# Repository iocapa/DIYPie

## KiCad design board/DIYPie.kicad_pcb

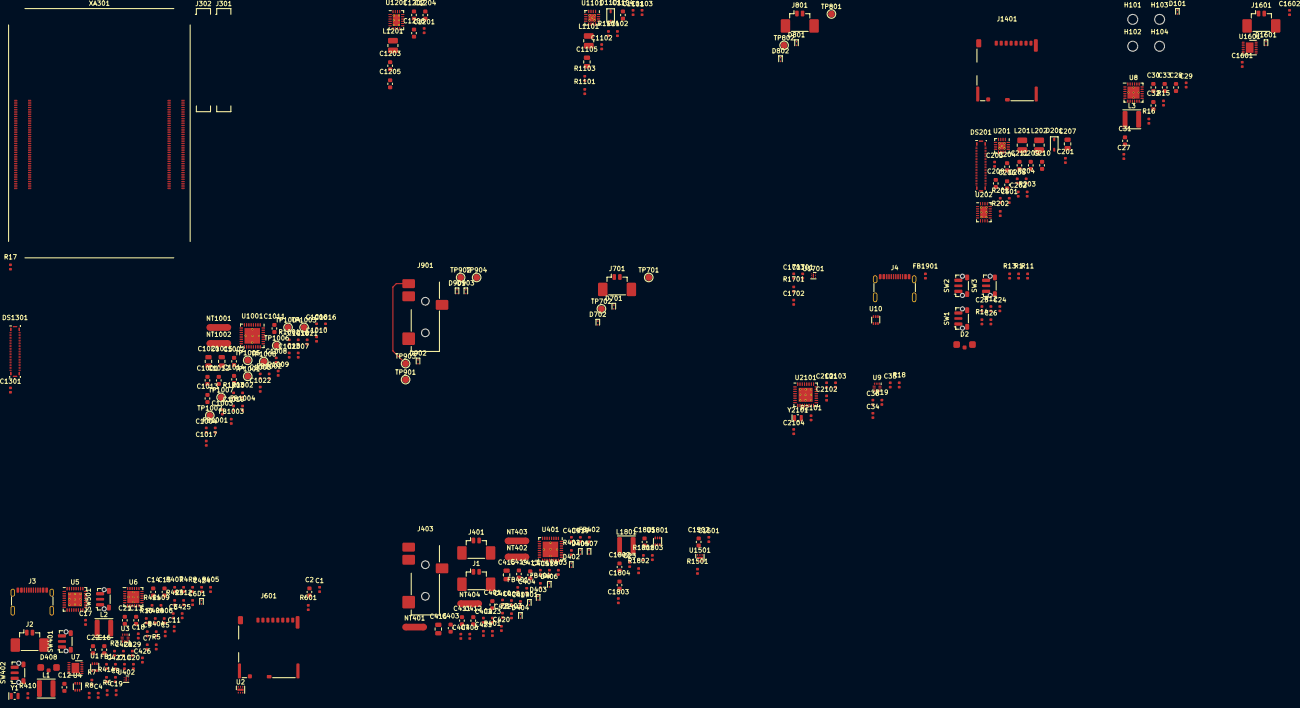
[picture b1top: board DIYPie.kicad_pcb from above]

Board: 6 copper layers, 289 parts (0 on the bottom side), 166 nets.

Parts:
C1, C20, C203, C405, C408, C417, C424, C425, C426, C1005, C1008, C1019, C1103, C1501, C1602, C1701, C1702, C1703: 470n; C_0402_1005Metric
C2, C13, C14, C15, C16, C21, C22, C28, C31, C32, C33, C209, C210, C211, C411, C412, C413, C414, C1011, C1012, C1013, C1014, C1204, C1205, C1206, C1502, C1804, C1805: 10u; C_0603_1608Metric
C3, C11, C17, C19, C34, C36, C1803: 220p; C_0402_1005Metric
C4, C5, C6, C10, C27, C35, C201, C202, C205, C501, C1101, C1102, C1201, C1301, C2101, C2104: 1u; C_0402_1005Metric
C7, C8, C2102, C2103: 12p; C_0402_1005Metric
C9, C29, C418, C419, C1018, C1023: 47n; C_0402_1005Metric
C12, C30, C204, C206, C208, C401, C403, C1001, C1002, C1104, C1202, C1203, C1802: 4u7; C_0603_1608Metric
C18, C23, C24, C25, C26, C402, C404, C406, C407, C409, C410, C427, C428, C429, C1003, C1004, C1006, C1007, C1009, C1010, C1601: 0u1; C_0402_1005Metric
C207, C1105: 4u7; C_0805_2012Metric
C415, C416, C1015, C1020: 47u; C_0805_2012Metric
C420, C421, C422, C423, C1016, C1017, C1021, C1022: 470p; C_0402_1005Metric
D1, D401, D402, D403, D404, D405, D406, D407, D701, D702, D801, D802, D901, D902, D903, D1601: DF2B7AFS; D_SOD-923
D2, D408: STATUS; KINGBRIGHT_APBA3010
D101: XBP1010-G; D_SOD-923
D201, D1101: PMEG4010CEJ; D_SOD-323F
DS201, DS1301: LPM035M407B; KYOCERA_245863050104829+
FB1, FB401, FB402, FB403, FB404, FB1001, FB1002, FB1003, FB1004, FB1901: 120R; L_0402_1005Metric
H101, H102, H103, H104: Hole; MountingHole_2.2mm_M2
J1: SPK_L; MOLEX_533980267
J2, J1601: BAT; MOLEX_533980267
J3, J4: MOLEX_2171790001
J301, J302: DF40C-100DS-0.4V(51); HIROSE_DF40C-100DS-0.4V(51)_NoPads
J401, J701, J801: SPK_R; MOLEX_533980267
J403, J901: HP; CUI_DEVICES_SJ-43514-SMT
J601, J1401: MOLEX_5033981892
L1, L2, L3, L1801: 1u; L_TYA4020
L201, L202, L1101, L1201: 4u7; L_1008_2520Metric
NT401, NT402, NT403, NT404, NT1001, NT1002: Net-Tie_2; NetTie-2_SMD_Pad1.5mm
R1, R11, R402, R403, R410, R411, R1001, R1003: 100R; R_0402_1005Metric
R3, R5, R6, R10, R15, R16, R18, R406, R407, R409: 10K; R_0402_1005Metric
R4, R7, R8, R19, R203, R405, R601, R1103, R1501, R1701, R1801, R1802: 732K; R_0402_1005Metric
R9, R12, R13, R14, R17, R408, R412, R413, R414, R1803: 100K; R_0402_1005Metric
R201, R204, R404, R1101, R1104, R2101: 34K; R_0402_1005Metric
R202, R1102: 82K; R_0402_1005Metric
R401, R1002: 2K2; R_0402_1005Metric
SW1, SW401: POWER; CKCOMPONENTS_PTS845VM20PSMTR4LFS
SW2, SW501: VOL+; CKCOMPONENTS_PTS845VM20PSMTR4LFS
SW3, SW402: VOL-; CKCOMPONENTS_PTS845VM20PSMTR4LFS
TP701, TP702, TP801, TP802, TP901, TP902, TP903, TP904, TP1001, TP1002, TP1003, TP1004, TP1005, TP1006, TP1007, TP1008: TestPoint; TestPoint_Pad_D1.5mm
U1, U1801: TPS61023; SOT-563
U2, U1501: MIC94305; TDFN1616-6LD-PL-1
U3, U9: FUSB303BTMX; ON_X2QFN-12_1.6x1.6mm_P0.4mm
U4, U10: DT1446-04V-7; SOT-563
U5, U2101: ATmega808-M; MICROCHIP_VQFN-32_RXB
U6, U8: BQ24259RGE; TI_BQ24259RGE
U7, U1601: MAX17260SETD+; MAXIM_TDFN-14-EP-T1433-2C
U201, U1101: TPS61176; TI_TPS61176RTE
U202, U1201: TPS65132W; TI_TPS65132WRVC
U401, U1001: TLV320AIC3110IRHB; TI_TLV320AIC3110
U402, U1701: AP7342; DIODES_X2-DFN1212-6
XA301: CM4; CM4_LOW_PROFILE_NoHoles
Y1, Y2101: 32K768; WE_830050789

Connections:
+1V8: C401.1, C402.1, C501.2, C1301.2, DS201.2 (VDDI), DS201.4 (VDDI), DS1301.2 (VDDI), DS1301.4 (VDDI), U401.3 (DVDD), XA301.88 (CM4_1.8V), XA301.90 (CM4_1.8V)
+3V3: C1.1, C4.2, C5.2, C10.2, C35.2, C202.2, C205.2, C403.1, C404.1, C425.1, C426.1, C1102.2, C1201.2, C2101.2, C2104.2, D2.1 (A), D408.1 (A), NT403.1, R3.1, R7.1, R10.1, R12.1, R13.1, R14.1, R18.1, R404.1, R406.1, R407.1, R409.1, R412.1, R413.1, R414.1, R601.1, R2101.1, U2.5 (VIN), U2.6 (VIN), U3.12 (VDD), U5.18 (AVDD), U5.28 (VDD), U9.12 (VDD), U201.15 (VIN), U202.4 (VIN), U401.2 (IOVDD), U402.1 (VO1), U402.2 (VO2), U1101.15 (VIN), U1201.4 (VIN), U2101.18 (AVDD), U2101.28 (VDD), XA301.78 (GPIO_VREF), XA301.84 (CM4_3.3V), XA301.86 (CM4_3.3V)
+5V: C6.2, C14.1, C15.1, C16.1, C19.2, C21.1, C22.1, C27.2, C32.1, C204.1, C206.1, C424.1, C1104.1, C1202.1, J3.A4 (VBUS), J3.A9 (VBUS), J3.B4 (VBUS), J3.B9 (VBUS), J4.A4 (VBUS), J4.A9 (VBUS), J4.B4 (VBUS), J4.B9 (VBUS), L1.2, L2.1, L201.1, L202.1, L1101.1, L1201.1, NT404.1, R8.1, U1.3 (VIN), U1.6 (VOUT), U3.4 (VBUS_DET), U4.5 (VBUS), U6.1 (VBUS), U6.13 (BAT), U6.14 (BAT), U6.15 (SYS), U6.16 (SYS), U6.24 (VBUS), U8.1 (VBUS), U8.13 (BAT), U8.14 (BAT), U8.24 (VBUS), U9.4 (VBUS_DET), U10.5 (VBUS), U402.5 (VIN), U402.6 (EN1), XA301.77 (+5V), XA301.79 (+5V), XA301.81 (+5V), XA301.83 (+5V), XA301.85 (+5V), XA301.87 (+5V)
/3V3 Regulators/EN2: R1701.1, U1701.4 (EN2)
/3V3 Regulators/VIN: C1701.1, U1701.5 (VIN), U1701.6 (EN1)
/3V3 Regulators/VOUT1: C1702.1, U1701.1 (VO1)
/3V3 Regulators/VOUT2: C1703.1, U1701.2 (VO2)
/5V Regulator/EN: C23.1, R1801.1, U1801.2 (EN)
/5V Regulator/VIN: C1802.1, L1801.1, U1801.3 (VIN)
/5V Regulator/VOUT: C1803.1, C1804.1, C1805.1, R1802.1, U1801.6 (VOUT)
/Audio CODEC/AVDD: C1006.1, C1009.1, C1011.1, C1013.1, U1001.17 (AVDD), U1001.28 (HPVDD)
/Audio CODEC/DVDD: C1002.1, C1004.1, U1001.3 (DVDD)
/Audio CODEC/HP_L: C1020.2, R1003.1
/Audio CODEC/HP_R: C1015.2, R1001.1
/Audio CODEC/IOVDD: C1001.1, C1003.1, U1001.2 (IOVDD)
/Audio CODEC/SPL_M: C1017.2, FB1002.1
/Audio CODEC/SPL_P: C1016.2, FB1001.1
/Audio CODEC/SPR_M: C1022.2, FB1004.1
/Audio CODEC/SPR_P: C1021.2, FB1003.1
/Audio CODEC/SPVDD: C1007.1, C1010.1, C1012.1, C1014.1, U1001.21 (SPLVDD), U1001.24 (SPRVDD)
/Audio CODEC/hpl: C1020.1, U1001.27 (HPL)
/Audio CODEC/hpr: C1015.1, U1001.30 (HPR)
/Audio CODEC/i2s_din: TP1007.1, U1001.4 (DOUT)
/Audio CODEC/i2s_dout: TP1006.1, U1001.5 (DIN)
/Audio CODEC/i2s_fs: TP1005.1, U1001.6 (WCLK)
/Audio CODEC/i2s_sclk: TP1004.1, U1001.7 (BCLK)
/Audio CODEC/int: TP1002.1, U1001.32 (GPIO1)
/Audio CODEC/mclk: TP1003.1, U1001.8 (MCLK)
/Audio CODEC/mic: C1019.2, U1001.14 (MIC1RP)
/Audio CODEC/micbias: R1002.2, U1001.12 (MICBIAS)
/Audio CODEC/micdet: C1019.1, R1002.1, U1001.11 (VOL/MICDET)
/Audio CODEC/reset: TP1001.1, U1001.31 (~RESET~)
/Audio CODEC/splm: FB1002.2, U1001.19 (SPLM)
/Audio CODEC/splp: FB1001.2, U1001.22 (SPLP)
/Audio CODEC/sprm: FB1004.2, U1001.23 (SPRM)
/Audio CODEC/sprp: FB1003.2, U1001.26 (SPRP)
/Audio/aud_hpl: C416.1, U401.27 (HPL)
/Audio/aud_hpr: C415.1, U401.30 (HPR)
/Audio/aud_mic: C417.1, U401.14 (MIC1RP)
/Audio/aud_micbias: R401.2, U401.12 (MICBIAS)
/Audio/aud_micdet: C417.2, D405.2 (A), J403.S, R401.1, U401.11 (VOL/MICDET)
/Audio/aud_splm: FB403.2, U401.19 (SPLM)
/Audio/aud_splp: FB404.2, U401.22 (SPLP)
/Audio/aud_sprm: FB401.2, U401.23 (SPRM)
/Audio/aud_sprp: FB402.2, U401.26 (SPRP)
/Backlight/disp_led+: C1105.1, D1101.1 (K), R1103.1
/Battery/scb_vbat_sns: C1601.1, U1601.6 (BATT)
/Bias/disp_avdd: C1204.1, U1201.15 (OUTP), U1201.16 (OUTP)
/Bias/disp_avee: C1206.1, U1201.9 (OUTN)
/Buttons & LEDs/scb_sw_pow: C24.1, R12.2, SW1.2
/Buttons & LEDs/scb_sw_vol+: C25.1, R13.2, SW2.2
/Buttons & LEDs/scb_sw_vol-: C26.1, R14.2, SW3.2
/Compute module 4/scb_global_en: R17.1, XA301.99 (GLOBAL_EN)
/Display1/disp_avdd: C210.1, DS201.3 (AVDD), U202.15 (OUTP), U202.16 (OUTP)
/Display1/disp_avee: C211.1, DS201.7 (AVEE), U202.9 (OUTN)
/Display1/disp_led1-: DS201.45 (LED1-), U201.11 (IFB1)
/Display1/disp_led2-: DS201.47 (LED2-), U201.7 (IFB4)
/Display1/disp_led+: C207.1, D201.1 (K), DS201.41 (LED+), R203.1
/Display1/disp_pwm: DS201.48 (LEDPWM), U201.1 (PWM/EN)
/Headpnones/HP_L: D901.2 (A), J901.T, TP901.1
/Headpnones/HP_R: D902.2 (A), J901.R1, TP902.1
/Headpnones/MIC: D903.2 (A), J901.S, TP903.1
/Left speaker/SP_M: D801.2 (A), J801.1, TP801.1
/Left speaker/SP_P: D802.2 (A), J801.2, TP802.1
/Memory/mem_pwr: R601.2, U2.4 (EN)
/Right speaker/SP_M: D701.2 (A), J701.1, TP701.1
/Right speaker/SP_P: D702.2 (A), J701.2, TP702.1
/SD Power/EN: R1501.2, U1501.4 (EN)
/SD Power/VIN: C1501.1, R1501.1, U1501.5 (VIN), U1501.6 (VIN)
/SD Power/VOUT: C1502.1, U1501.1 (VOUT), U1501.2 (VOUT)
/System Control Block/scb_3v3a_en: R405.1, U402.4 (EN2)
/System Control Block/scb_5v_en: C17.2, R7.2, U1.2 (EN)
/System Control Block/scb_dbg_rst: R404.2, U5.26 (PF6/~RESET~)
/System Control Block/scb_global_en: R408.1, U5.14 (PD4)
/System Control Block/scb_int_bc: R406.2, U5.12 (PD2), U6.7 (INT)
/System Control Block/scb_int_fg: R10.2, U5.10 (PD0), U7.12 (ALRT)
/System Control Block/scb_int_usbc: R3.2, U3.6 (INT_N/OUT3), U5.11 (PD1)
/System Control Block/scb_led_g: R411.2, U5.23 (PF3)
/System Control Block/scb_loc_scl: R407.2, U3.8 (SCL/OUT2), U5.1 (PA3), U6.5 (SCL), U7.14 (SCL)
/System Control Block/scb_loc_sda: R409.2, U3.7 (SDA/OUT1), U5.32 (PA2), U6.6 (SDA), U7.13 (SDA)
/System Control Block/scb_sw_pow: C427.1, R412.2, SW401.2
/System Control Block/scb_sw_vol+: C428.1, R413.2, SW501.2
/System Control Block/scb_sw_vol-: C429.1, R414.2, SW402.2
/System Control Block/scb_usb_cc1: C3.2, J3.A5 (CC1), U3.1 (CC1), U4.6 (I/O4)
/System Control Block/scb_usb_cc2: C11.2, J3.B5 (CC2), U3.2 (CC2), U4.3 (I/O2)
/System Control Block/scb_usb_dm: J3.A7 (D-), J3.B7 (D-), U4.1 (I/O1)
/System Control Block/scb_usb_dp: J3.A6 (D+), J3.B6 (D+), U4.4 (I/O3)
/System Control Block/scb_vbat_sns: C18.1, U7.6 (BATT)
/System controller/scb_dbg_rst: R2101.2, U2101.26 (PF6/~RESET~)
/Type-C Controller/scb_int_usbc: R18.2, U9.6 (INT_N/OUT3)
/Type-C Controller/scb_usb_cc1: C34.2, U9.1 (CC1)
/Type-C Controller/scb_usb_cc2: C36.2, U9.2 (CC2)
/USB Type-C/scb_usb_cc1: J4.A5 (CC1), U10.6 (I/O4)
/USB Type-C/scb_usb_cc2: J4.B5 (CC2), U10.3 (I/O2)
/USB Type-C/scb_usb_dm: J4.A7 (D-), J4.B7 (D-), U10.1 (I/O1)
/USB Type-C/scb_usb_dp: J4.A6 (D+), J4.B6 (D+), U10.4 (I/O3)
GND: C1.2, C2.2, C3.1, C4.1, C5.1, C6.1, C7.2, C8.2, C10.1, C11.1, C12.2, C13.2, C14.2, C15.2, C16.2, C17.1, C18.2, C20.2, C21.2, C22.2, C23.2, C24.2, C25.2, C26.2, C27.1, C28.2, C30.2, C31.2, C32.2, C33.2, C34.1, C35.1, C36.1, C201.2, C202.1, C203.2, C204.2, C205.1, C206.2, C207.2, C209.2, C210.2, C211.2, C401.2, C402.2, C403.2, C404.2, C424.2, C425.2, C426.2, C427.2, C428.2, C429.2, C501.1, C1001.2, C1002.2, C1003.2, C1004.2, C1101.2, C1102.1, C1103.2, C1104.2, C1105.2, C1201.1, C1202.2, C1204.2, C1205.2, C1206.2, C1301.1, C1501.2, C1502.2, C1601.2, C1602.2, C1701.2, C1702.2, C1703.2, C1802.2, C1804.2, C1805.2, C2101.1, C2102.2, C2103.2, C2104.1, D1.2 (A), D701.1 (A), D702.1 (A), D801.1 (A), D802.1 (A), D901.1 (A), D902.1 (A), D903.1 (A), D1601.2 (A), DS201.1 (GND), DS201.5 (GND), DS201.9 (GND), DS201.10 (GND), DS201.15 (GND), DS201.16 (GND), DS201.21 (GND), DS201.22 (GND), DS201.23 (DSI_D2P_B), DS201.25 (DSI_D2N_B), DS201.27 (GND), DS201.28 (GND), DS201.29 (DSI_CLKP_B), DS201.30 (DSI_D1P_B), DS201.31 (DSI_CLKN_B), DS201.32 (DSI_D1N_B), DS201.33 (GND), DS201.34 (GND), DS201.35 (DSI_D3P_B), DS201.36 (DSI_D0P_B), DS201.37 (DSI_D3N_B), DS201.38 (DSI_D0N_B), DS201.39 (GND), DS201.40 (GND), DS201.43 (GND), DS201.46 (GND), DS201.49 (GND), DS201.50 (GND), DS201.MP, DS1301.1 (GND), DS1301.5 (GND), DS1301.9 (GND), DS1301.10 (GND), DS1301.15 (GND), DS1301.16 (GND), DS1301.21 (GND), DS1301.22 (GND), DS1301.23 (DSI_D2P_B), DS1301.25 (DSI_D2N_B), DS1301.27 (GND), DS1301.28 (GND), DS1301.29 (DSI_CLKP_B), DS1301.30 (DSI_D1P_B), DS1301.31 (DSI_CLKN_B), DS1301.32 (DSI_D1N_B), DS1301.33 (GND), DS1301.34 (GND), DS1301.35 (DSI_D3P_B), DS1301.36 (DSI_D0P_B), DS1301.37 (DSI_D3N_B), DS1301.38 (DSI_D0N_B), DS1301.39 (GND), DS1301.40 (GND), DS1301.43 (GND), DS1301.46 (GND), DS1301.49 (GND), DS1301.50 (GND), DS1301.MP, FB1.2, FB1901.2, J2.1, J2.MP (MountPin), J3.A1 (GND), J3.A12 (GND), J3.B1 (GND), J3.B12 (GND), J4.A1 (GND), J4.A12 (GND), J4.B1 (GND), J4.B12 (GND), J601.6 (VSS), J601.11 (SHIELD), J701.MP (MountPin), J801.MP (MountPin), J1401.6 (VSS), J1401.11 (SHIELD), J1601.1, J1601.MP (MountPin), NT401.2, NT402.2, NT1001.2, NT1002.2, R4.2, R6.2, R9.2, R16.2, R17.2, R19.2, R201.2, R202.2, R204.2, R405.2, R408.2, R1101.2, R1102.2, R1104.2, R1701.2, R1801.2, R1803.2, SW1.1, SW1.3, SW1.MP, SW2.1, SW2.3, SW2.MP, SW3.1, SW3.3, SW3.MP, SW401.1, SW401.3, SW401.MP, SW402.1, SW402.3, SW402.MP, SW501.1, SW501.3, SW501.MP, TP1008.1, U1.4 (GND), U2.3 (GND), U2.7 (PAD), U3.10 (GND), U3.11 (EN_N), U4.2 (GND), U5.19 (GND), U5.29 (GND), U5.33 (PAD), U6.9 (~CE~), U6.10 (ILIM), U6.17 (PGND), U6.18 (PGND), U6.25 (PAD), U7.8 (GND), U7.9 (CSPL), U7.15 (PAD), U8.9 (~CE~), U8.10 (ILIM), U8.17 (PGND), U8.18 (PGND), U8.25 (PAD), U9.10 (GND), U9.11 (EN_N), U10.2 (GND), U201.5 (IFB6), U201.6 (IFB5), U201.8 (GND), U201.9 (IFB3), U201.10 (IFB2), U201.13 (PGND), U201.17 (PAD), U202.1 (PGND), U202.2 (PGND), U202.3 (AGND), U202.11 (PGND), U202.12 (PGND), U202.17 (AGND), U202.21 (PAD), U401.1 (IOVSS), U401.18 (DVSS), U402.3 (GND), U402.7 (PAD), U1001.1 (IOVSS), U1001.18 (DVSS), U1101.5 (IFB6), U1101.6 (IFB5), U1101.8 (GND), U1101.9 (IFB3), U1101.10 (IFB2), U1101.13 (PGND), U1101.17 (PAD), U1201.1 (PGND), U1201.2 (PGND), U1201.3 (AGND), U1201.11 (PGND), U1201.12 (PGND), U1201.17 (AGND), U1201.21 (PAD), U1501.3 (GND), U1501.7 (PAD), U1601.8 (GND), U1601.9 (CSPL), U1601.15 (PAD), U1701.3 (GND), U1701.7 (PAD), U1801.4 (GND), U2101.19 (GND), U2101.29 (GND), U2101.33 (PAD), XA301.1 (GND), XA301.2 (GND), XA301.7 (GND), XA301.8 (GND), XA301.13 (GND), XA301.14 (GND), XA301.22 (GND), XA301.23 (GND), XA301.32 (GND), XA301.33 (GND), XA301.42 (GND), XA301.43 (GND), XA301.52 (GND), XA301.53 (GND), XA301.59 (GND), XA301.60 (GND), XA301.65 (GND), XA301.66 (GND), XA301.71 (GND), XA301.74 (GND), XA301.98 (GND), XA301.107 (GND), XA301.108 (GND), XA301.113 (GND), XA301.114 (GND), XA301.119 (GND), XA301.120 (GND), XA301.125 (GND), XA301.126 (GND), XA301.131 (GND), XA301.132 (GND), XA301.137 (GND), XA301.138 (GND), XA301.144 (GND), XA301.150 (GND), XA301.155 (GND), XA301.156 (GND), XA301.161 (GND), XA301.162 (GND), XA301.167 (GND), XA301.168 (GND), XA301.173 (GND), XA301.174 (GND), XA301.179 (GND), XA301.180 (GND), XA301.185 (GND), XA301.186 (GND), XA301.191 (GND), XA301.192 (GND), XA301.197 (GND), XA301.198 (GND)
GNDA: C405.2, C406.2, C407.2, C408.2, C409.2, C410.2, C411.2, C412.2, C413.2, C414.2, C418.2, C419.2, C420.1, C421.1, C422.1, C423.1, C1005.2, C1006.2, C1007.2, C1008.2, C1009.2, C1010.2, C1011.2, C1012.2, C1013.2, C1014.2, C1016.1, C1017.1, C1018.2, C1021.1, C1022.1, C1023.2, D401.1 (A), D402.1 (A), D403.1 (A), D404.1 (A), D405.1 (A), D406.1 (A), D407.1 (A), J1.MP (MountPin), J401.MP (MountPin), J403.R2, J901.R2, NT401.1, NT402.1, NT1001.1, NT1002.1, TP904.1, U401.16 (AVSS), U401.20 (SPLVSS), U401.25 (SPRVSS), U401.29 (HPVSS), U401.33 (PAD), U1001.16 (AVSS), U1001.20 (SPLVSS), U1001.25 (SPRVSS), U1001.29 (HPVSS), U1001.33 (PAD)
unnamed: C2.1, J601.4 (VDD), U2.1 (VOUT), U2.2 (VOUT)
unnamed: C7.1, U5.20 (PF0/TOSC1), Y1.2
unnamed: C8.1, U5.21 (PF1/TOSC2), Y1.1
unnamed: C9.1, L1.1, U6.19 (SW), U6.20 (SW)
unnamed: C9.2, U6.21 (BTST)
unnamed: C12.1, R5.1, U6.22 (REGN)
unnamed: C13.1, U6.23 (PMID)
unnamed: C19.1, R8.2, R9.1, U1.1 (FB)
unnamed: C20.1, U7.11 (REG)
unnamed: C28.1, U8.23 (PMID)
unnamed: C29.1, L3.1, U8.19 (SW), U8.20 (SW)
unnamed: C29.2, U8.21 (BTST)
unnamed: C30.1, R15.1, U8.22 (REGN)
unnamed: C31.1, C33.1, L3.2, U8.15 (SYS), U8.16 (SYS)
unnamed: C201.1, U201.2 (VLDO)
unnamed: C203.1, U201.4 (COMP)
unnamed: C208.1, U202.13 (CFLY1)
unnamed: C208.2, U202.10 (CFLY2)
unnamed: C209.1, U202.14 (REG), U202.18 (REG)
unnamed: C405.1, U401.13 (MIC1LP)
unnamed: C406.1, C409.1, C411.1, C413.1, NT403.2, U401.17 (AVDD), U401.28 (HPVDD)
unnamed: C407.1, C410.1, C412.1, C414.1, NT404.2, U401.21 (SPLVDD), U401.24 (SPRVDD)
unnamed: C408.1, U401.15 (MIC1LM)
unnamed: C415.2, D404.2 (A), J403.R1, R403.1
unnamed: C416.2, D401.2 (A), J403.T, R402.1
unnamed: C418.1, R402.2
unnamed: C419.1, R403.2
unnamed: C420.2, D402.2 (A), FB402.1, J401.2
unnamed: C421.2, D403.2 (A), FB404.1, J1.2
unnamed: C422.2, D406.2 (A), FB401.1, J401.1
unnamed: C423.2, D407.2 (A), FB403.1, J1.1
unnamed: C1005.1, U1001.13 (MIC1LP)
unnamed: C1008.1, U1001.15 (MIC1LM)
unnamed: C1018.1, R1001.2
unnamed: C1023.1, R1003.2
unnamed: C1101.1, U1101.2 (VLDO)
unnamed: C1103.1, U1101.4 (COMP)
unnamed: C1203.1, U1201.13 (CFLY1)
unnamed: C1203.2, U1201.10 (CFLY2)
unnamed: C1205.1, U1201.14 (REG), U1201.18 (REG)
unnamed: C1602.1, U1601.11 (REG)
unnamed: C1803.2, R1802.2, R1803.1, U1801.1 (FB)
unnamed: C2102.1, U2101.20 (PF0/TOSC1), Y2101.2
unnamed: C2103.1, U2101.21 (PF1/TOSC2), Y2101.1
unnamed: D1.1 (A), J2.2
unnamed: D2.2 (RK), R1.2
unnamed: D2.3 (GK), R11.1
unnamed: D201.2 (A), L201.2, U201.14 (SW)
unnamed: D408.2 (RK), R410.2
unnamed: D408.3 (GK), R411.1
unnamed: D1101.2 (A), L1101.2, U1101.14 (SW)
unnamed: D1601.1 (A), J1601.2
unnamed: FB1.1, J3.S1 (SHIELD)
unnamed: FB1901.1, J4.S1 (SHIELD)
unnamed: L2.2, U1.5 (SW)
unnamed: L202.2, U202.19 (SW), U202.20 (SW)
unnamed: L1201.2, U1201.19 (SW), U1201.20 (SW)
unnamed: L1801.2, U1801.5 (SW)
unnamed: R4.1, U3.5 (ADDR/ORIENT)
unnamed: R5.2, R6.1, U6.11 (TS)
unnamed: R15.2, R16.1, U8.11 (TS)
unnamed: R19.1, U9.5 (ADDR/ORIENT)
unnamed: R201.1, U201.3 (ISET)
unnamed: R202.1, U201.16 (MODE/FAULT)
unnamed: R203.2, R204.1, U201.12 (OVP)
unnamed: R1101.1, U1101.3 (ISET)
unnamed: R1102.1, U1101.16 (MODE/FAULT)
unnamed: R1103.2, R1104.1, U1101.12 (OVP)

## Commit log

2021-04-04 Initial board
2021-06-23 Migrated to 5.99 (and other changes)
2021-06-23 Added temporary footprints to gitignore
2021-06-23 Prepared kibot makefile for kicad6 (Not working)
2021-06-27 Added testpoints and other fixes
